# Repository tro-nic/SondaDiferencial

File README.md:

<div align="center">

# Sonda Diferencial de Baja Tensión de hasta 250Vp (seno: 176,78Vrms) @ 100kHz

*Un proyecto para mediciones seguras y precisas con osciloscopio. Basado en componentes disponibles en cualquier laboratorio o tienda de electrónica.*

</div>

---

## 1. Descripción del Proyecto

Esta **Sonda Diferencial** ha sido diseñada para permitir mediciones de señales flotantes usando un solo canal de un osciloscopio convencional sin riesgo de cortocircuitos a tierra o daños en el equipo de medición.

El circuito atenúa y convierte señales diferenciales en una señal referenciada a masa (*single-ended*) apta para las entradas estándar BNC (Vo: 3Vpp).

### Esquemático del Circuito

<div align="center">
  
  <p><em>Figura 1: Esquemático general del circuito de la sonda diferencial.</em></p>
</div>

---

## 2. Licencia y Restricciones

Este proyecto está bajo la licencia **Creative Commons Attribution-NonCommercial-ShareAlike 3.0 Unported (CC BY-NC-SA 3.0)**.

* **Atribución (BY):** Debe dar crédito de manera adecuada, brindar un enlace a la licencia e indicar si se han realizado cambios.
* **No Comercial (NC):** <u>No puede utilizar este material para una finalidad comercial</u> ni para obtener una ventaja monetaria directa/indirecta sin la autorización previa del autor.
* **Compartir Igual (SA):** Si remezcla, transforma o crea a partir del material, debe distribuir sus contribuciones bajo la misma licencia que el original.

---

## 3. Lista de Materiales (BOM)

A continuación se detalla la lista completa de componentes extraída directamente de KiCad:

| Designador | Valor / Descripción | Cantidad | Encapsulado / Footprint |
| :--- | :--- | :---: | :--- |
| **U1, U2** | TL082 (Op-Amp JFET Dual) | 2 | Package_DIP:DIP-8_W7.62mm_Socket |
| **U3** | LM358 (Op-Amp Dual) | 1 | Package_DIP:DIP-8_W7.62mm_Socket |
| **Q1** | MMBT2222A (Transistor NPN) | 1 | Package_TO_SOT_SMD:SOT-23 |
| **D1** | Z8V2 (Diodo Zener 8.2V) | 1 | Diode_THT:D_DO-41_SOD81_P12.70mm |
| **D2** | SM4007 (Diodo Rectificador) | 1 | Diode_SMD:D_MELF |
| **D3, D4, D9** | 1N4733A (Diodo Zener 5.1V) | 3 | Diode_THT:D_DO-41_SOD81_P10.16mm |
| **D5, D6, D7, D8** | LL4148 (Diodo de Señal) | 4 | Diode_SMD:D_MiniMELF |
| **D10** | LED 3mm (Power ON) | 1 | LED_THT:LED_D3.0mm |
| **D11** | LED 3mm (Low Battery) | 1 | LED_THT:LED_D3.0mm |
| **C1, C9, C13, C16, C19** | 10uF (Electrolítico) | 5 | Capacitor_THT:CP_Radial_D5.0mm_P2.00mm |
| **C10** | 100uF (Electrolítico) | 1 | Capacitor_THT:CP_Radial_D8.0mm_P3.50mm |
| **C11, C14, C17** | 1uF (Electrolítico) | 3 | Capacitor_THT:CP_Radial_D4.0mm_P2.00mm |
| **C3, C5, C8, C12, C15, C18** | 100nF | 6 | Capacitor_SMD:C_1206_3216Metric |
| **C2, C7** | 1nF | 2 | Capacitor_SMD:C_1206_3216Metric |
| **C4, C6** | Compensación | 2 | Capacitor_SMD:C_1206_3216Metric |
| **R3, R6** | 1M (Resistencia Alto Voltaje) | 2 | Resistor_THT:R_Axial_DIN0411 |
| **R4, R5, R8, R9, R11, R13** | 10k | 6 | Resistor_SMD:R_1206_3216Metric |
| **R15, R16** | 4k7 | 2 | Resistor_SMD:R_1206_3216Metric |
| **R7, R10** | 220 | 2 | Resistor_SMD:R_1206_3216Metric |
| **R21, R22** | 0 (Jumper) | 2 | Resistor_SMD:R_1206_3216Metric |
| **R1** | 470 | 1 | Resistor_SMD:R_1206_3216Metric |
| **R2** | 100k | 1 | Resistor_SMD:R_1206_3216Metric |
| **R12** | 100 | 1 | Resistor_SMD:R_1206_3216Metric |
| **R14** | 2k2 | 1 | Resistor_SMD:R_1206_3216Metric |
| **R17** | 22k | 1 | Resistor_SMD:R_1206_3216Metric |
| **R18** | 33k | 1 | Resistor_SMD:R_1206_3216Metric |
| **R19** | 1.2k | 1 | Resistor_SMD:R_1206_3216Metric |
| **R20** | 910 | 1 | Resistor_SMD:R_1206_3216Metric |
| **RV1, RV2** | 1k (Trimmer) | 2 | Potentiometer_THT:Potentiometer_Piher_PT-6-V |
| **J1** | Conector BNC Salida | 1 | Connector_Coaxial:BNC_Amphenol_B6252HB |
| **J2** | Clema 2P Alimentación 9V | 1 | TerminalBlock_MX126-5.0-02P |
| **J3, J4** | Pin Header +Vi / -Vi | 2 | Connector_PinHeader_2.54mm_1x01 |

<div align="center">
  
</div>

---

## 4. Cálculos del Sistema

* **Cálculos de alimentación del TL082:** 
  El voltaje efectivo que maneja el OP-AMP debe estar dentro de los márgenes de alimentación. Configurado diferencialmente con 8Vpp, entrega un `Vo_max = 5Vpp` (referenciado a tierra virtual de `+/- 2.5Vp`).
* **Voltaje pico de salida:** Debe ser `<= 5V` para adaptarse al rango de entrada de los osciloscopios convencionales.
* **Consumo total estimado:** 
  * Regulador: 2mA
  * Amplificador diferencial: 7mA
  * Buffer: 4mA
  * GND Virtual: 4mA
  * Detector de voltaje: 5mA
  * LED Rojo (Low Batt): 2.5mA
  * LED Verde (Power ON): 2.5mA
  * **Total:** `27mA` / **Potencia:** `221mW` (< 230mW requeridos).

---

## 5. Aplicaciones

* Medición en fuentes de alimentación conmutadas (SMPS) y etapas de potencia.
* Análisis de variadores de frecuencia (VFD) y drivers de motores.
* Diseño y prueba de circuitos Inverter y convertidores DC-DC.
* Medición segura en líneas de corriente alterna (AC) sin aislar el osciloscopio de tierra.

---

## 6. Demostración de Uso

1. Conecte la salida BNC de la sonda diferencial al Canal 1 de su osciloscopio mediante un cable coaxial de 50&Omega;.
2. Alimente la sonda (batería interna de 9V). El umbral de indicador de batería baja (*low-batt*) está calculado en 8.3Vdc.
3. Seleccione el factor de atenuación correcto en el osciloscopio (ej. 100x).
4. Conecte las puntas de prueba a los puntos flotantes de su circuito.

<div align="center">
  
  <p><em>Figura 2: Prueba de la sonda midiendo una señal en etapa de potencia.</em></p>
</div>

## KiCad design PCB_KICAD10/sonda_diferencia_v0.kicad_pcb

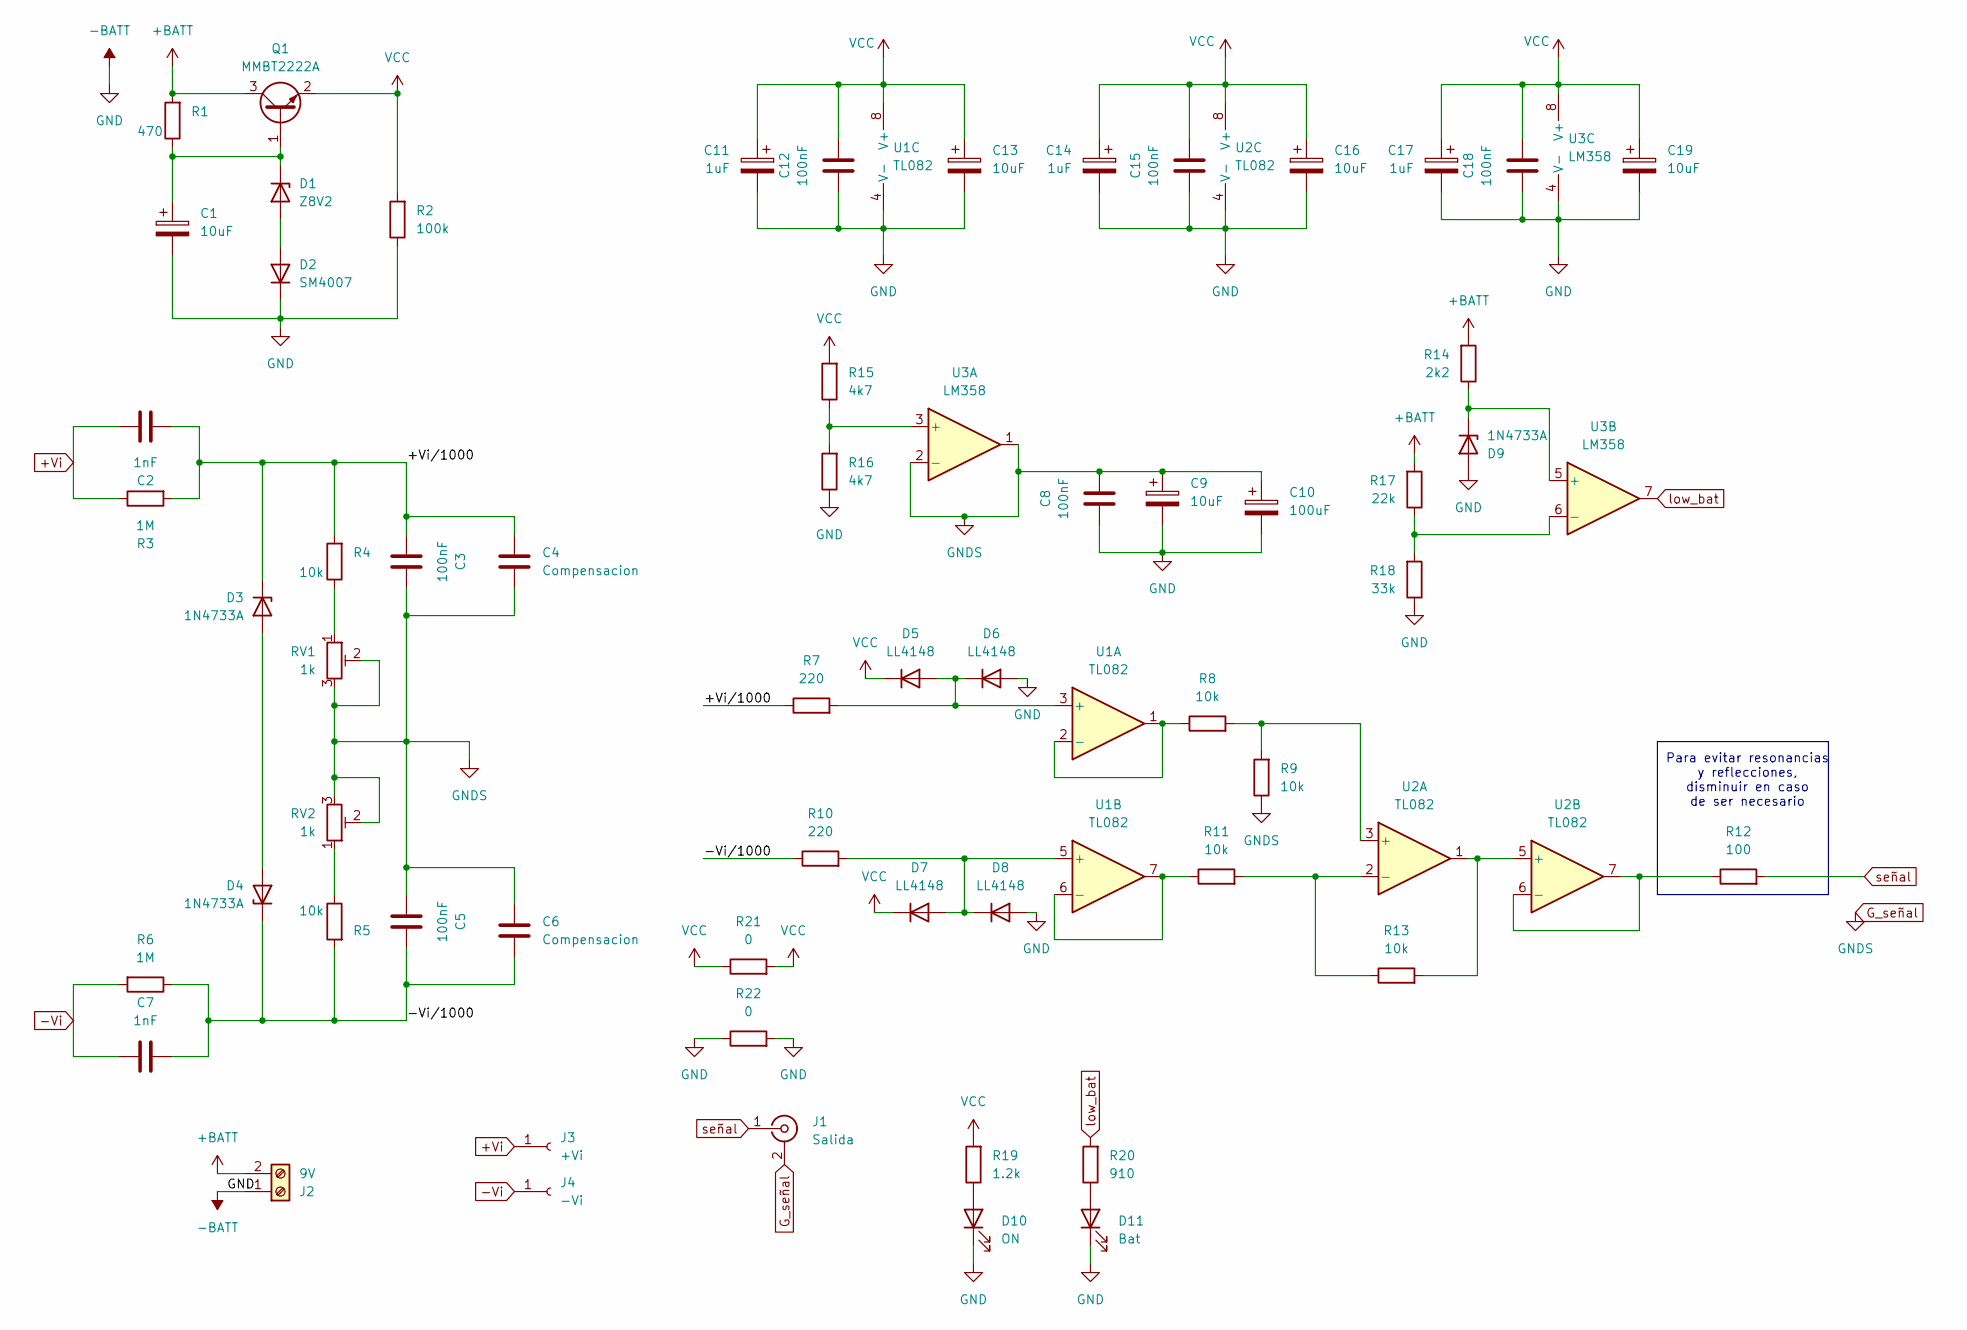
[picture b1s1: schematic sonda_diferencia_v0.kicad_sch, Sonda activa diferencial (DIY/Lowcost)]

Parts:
C1, C9, C13, C16, C19: 10uF; CP_Radial_D5.0mm_P2.00mm
C2, C7: 1nF; C_1206_3216Metric_Pad1.33x1.80mm_HandSolder
C3, C5, C8, C12, C15, C18: 100nF; C_1206_3216Metric_Pad1.33x1.80mm_HandSolder
C4, C6: Compensacion; C_1206_3216Metric_Pad1.33x1.80mm_HandSolder
C10: 100uF; CP_Radial_D8.0mm_P3.50mm
C11, C14, C17: 1uF; CP_Radial_D4.0mm_P2.00mm
D1: Z8V2; D_DO-41_SOD81_P12.70mm_Horizontal
D2: SM4007; D_MELF
D3, D4, D9: 1N4733A; D_DO-41_SOD81_P10.16mm_Horizontal
D5, D6, D7, D8: LL4148; D_MiniMELF
D10: ON; LED_D3.0mm
D11: Bat; LED_D3.0mm
J1: Salida; BNC_Amphenol_B6252HB-NPP3G-50_Horizontal
J2: 9V; TerminalBlock_MaiXu_MX126-5.0-02P_1x02_P5.00mm
J3: +Vi; PinHeader_1x01_P2.54mm_Vertical
J4: -Vi; PinHeader_1x01_P2.54mm_Vertical
Q1: MMBT2222A; SOT-23
R1: 470; R_1206_3216Metric_Pad1.30x1.75mm_HandSolder
R2: 100k; R_1206_3216Metric_Pad1.30x1.75mm_HandSolder
R3, R6: 1M; R_Axial_DIN0411_L9.9mm_D3.6mm_P12.70mm_Horizontal
R4, R5, R8, R9, R11, R13: 10k; R_1206_3216Metric_Pad1.30x1.75mm_HandSolder
R7, R10: 220; R_1206_3216Metric_Pad1.30x1.75mm_HandSolder
R12: 100; R_1206_3216Metric_Pad1.30x1.75mm_HandSolder
R14: 2k2; R_1206_3216Metric_Pad1.30x1.75mm_HandSolder
R15, R16: 4k7; R_1206_3216Metric_Pad1.30x1.75mm_HandSolder
R17: 22k; R_1206_3216Metric_Pad1.30x1.75mm_HandSolder
R18: 33k; R_1206_3216Metric_Pad1.30x1.75mm_HandSolder
R19: 1.2k; R_1206_3216Metric_Pad1.30x1.75mm_HandSolder
R20: 910; R_1206_3216Metric_Pad1.30x1.75mm_HandSolder
R21, R22: 0; R_1206_3216Metric_Pad1.30x1.75mm_HandSolder
RV1, RV2: 1k; Potentiometer_Piher_PT-6-V_Vertical
U1, U2: TL082; DIP-8_W7.62mm_Socket
U3: LM358; DIP-8_W7.62mm_Socket

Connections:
+BATT: J2.2, Q1.3 (C), R1.2, R14.2, R17.2
+Vi: C2.1, J3.1 (Pin_1_1), R3.1
-BATT: C1.2, C8.1, C9.2, C10.2, C11.2, C12.1, C13.2, C14.2, C15.1, C16.2, C17.2, C18.1, C19.2, D2.1 (K), D6.2 (A), D8.2 (A), D9.2 (A), D10.1 (K), D11.1 (K), J2.1, R2.1, R16.1, R18.1, R22.1, R22.2, U1.4 (V-), U2.4 (V-), U3.4 (V-)
-Vi: C7.1, J4.1 (Pin_1_1), R6.2
/+Vi/1000: C2.2, C3.2, C4.2, D3.1 (K), R3.2, R4.2, R7.1
/-Vi/1000: C5.2, C6.1, C7.2, D4.1 (K), R5.2, R6.1, R10.1
unnamed: D1.2 (A), D2.2 (A)
unnamed: C1.1, D1.1 (K), Q1.1 (B), R1.1
unnamed: D5.2 (A), D6.1 (K), R7.2, U1.3 (+)
unnamed: D7.2 (A), D8.1 (K), R10.2, U1.5 (+)
unnamed: D9.1 (K), R14.1, U3.5 (+)
unnamed: D10.2 (A), R19.1
unnamed: D11.2 (A), R20.1
unnamed: R4.1, RV1.1
unnamed: R5.1, RV2.1
unnamed: R8.1, U1.1, U1.2 (-)
unnamed: R11.1, U1.6 (-), U1.7
unnamed: R8.2, R9.2, U2.3 (+)
unnamed: R11.2, R13.1, U2.2 (-)
unnamed: R13.2, U2.1, U2.5 (+)
unnamed: R12.1, U2.6 (-), U2.7
unnamed: R15.1, R16.2, U3.3 (+)
unnamed: R17.1, R18.2, U3.6 (-)
VCC: C11.1, C12.2, C13.1, C14.1, C15.2, C16.1, C17.1, C18.2, C19.1, D5.1 (K), D7.1 (K), Q1.2 (E), R2.2, R15.2, R19.2, R21.1, R21.2, U1.8 (V+), U2.8 (V+), U3.8 (V+)
low_bat: R20.2, U3.7
señal: J1.1 (In), R12.2

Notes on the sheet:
Para evitar resonancias y reflecciones, disminuir en caso de ser necesario

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
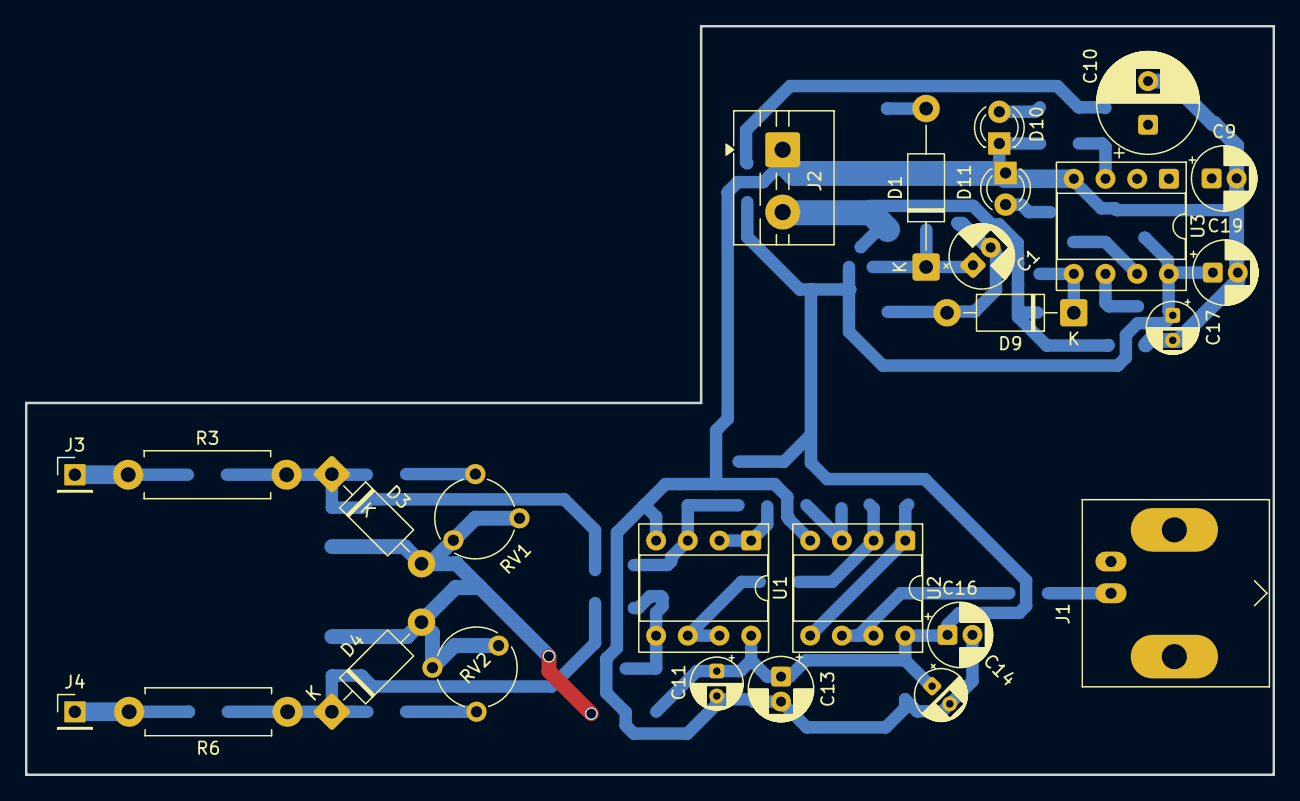
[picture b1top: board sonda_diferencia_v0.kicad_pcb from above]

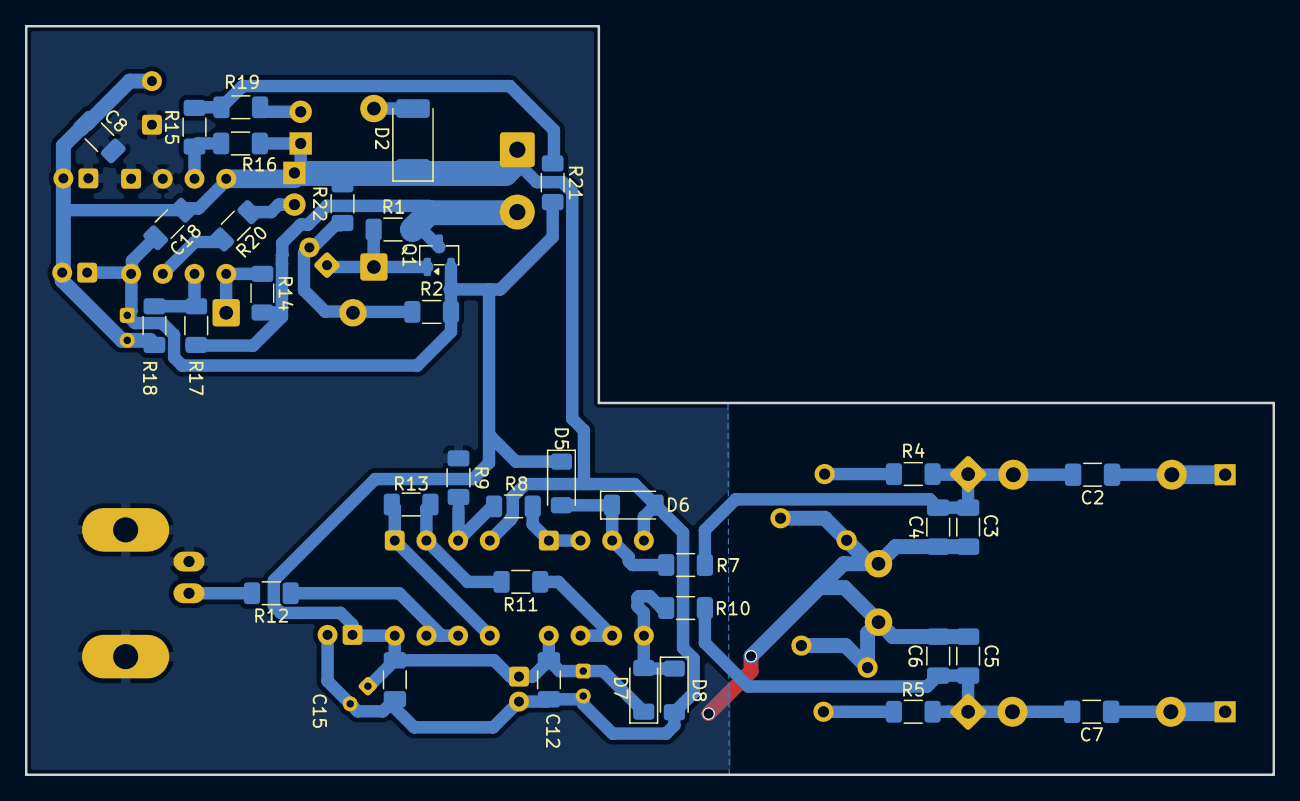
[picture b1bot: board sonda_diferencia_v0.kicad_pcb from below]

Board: 2 copper layers, 100.0 x 60.0 mm, 62 parts (36 on the bottom side), 27 nets.

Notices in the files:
README.md:
Licencia: CC BY-NC-SA 3.0
